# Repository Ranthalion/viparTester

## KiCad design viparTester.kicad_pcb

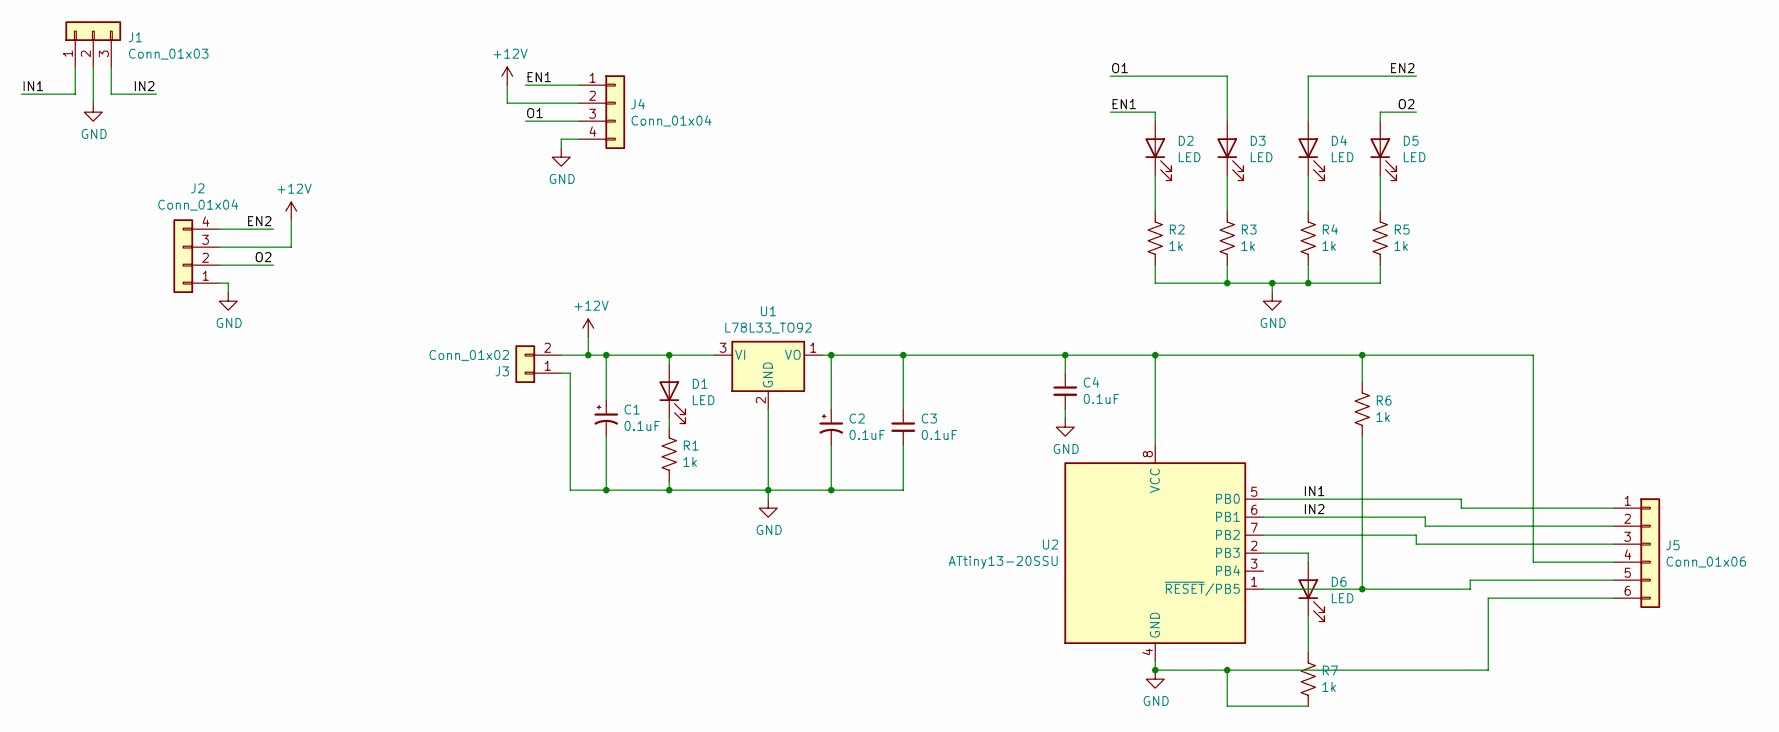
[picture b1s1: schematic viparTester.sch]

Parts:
C1, C2: 0.1uF; CP_Radial_D5.0mm_P2.00mm
C3, C4: 0.1uF; C_1206_3216Metric_Pad1.33x1.80mm_HandSolder
D1, D2, D3, D4, D5, D6: LED; LED_1206_3216Metric_Pad1.42x1.75mm_HandSolder
J1: Conn_01x03; PinSocket_1x03_P2.54mm_Vertical
J2, J4: Conn_01x04; PinSocket_1x04_P2.54mm_Vertical
J3: Conn_01x02; PinSocket_1x02_P2.54mm_Vertical
J5: Conn_01x06; PinSocket_1x06_P2.54mm_Vertical
R1, R2, R3, R4, R5, R6, R7: 1k; R_1206_3216Metric_Pad1.30x1.75mm_HandSolder
U1: L78L33_TO92; TO-92_Inline
U2: ATtiny13-20SSU; SOIC-8_3.9x4.9mm_P1.27mm

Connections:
+12V: C1.1, D1.2 (A), J2.3, J3.2, J4.2, U1.3 (VI)
/EN1: D2.2 (A), J4.1
/EN2: D4.2 (A), J2.4
/IN1: J1.1, J5.1, U2.5 (PB0)
/IN2: J1.3, J5.2, U2.6 (PB1)
/O1: D3.2 (A), J4.3
/O2: D5.2 (A), J2.2
GND: C1.2, C2.2, C3.2, C4.2, J1.2, J2.1, J3.1, J4.4, J5.6, R1.2, R2.2, R3.2, R4.2, R5.2, R7.2, U1.2 (GND), U2.4 (GND)
unnamed: C2.1, C3.1, C4.1, J5.4, R6.1, U1.1 (VO), U2.8 (VCC)
unnamed: D1.1 (K), R1.1
unnamed: D2.1 (K), R2.1
unnamed: D3.1 (K), R3.1
unnamed: D4.1 (K), R4.1
unnamed: D5.1 (K), R5.1
unnamed: D6.1 (K), R7.1
unnamed: D6.2 (A), U2.2 (PB3)
unnamed: J5.3, U2.7 (PB2)
unnamed: J5.5, R6.2, U2.1 (~RESET~/PB5)

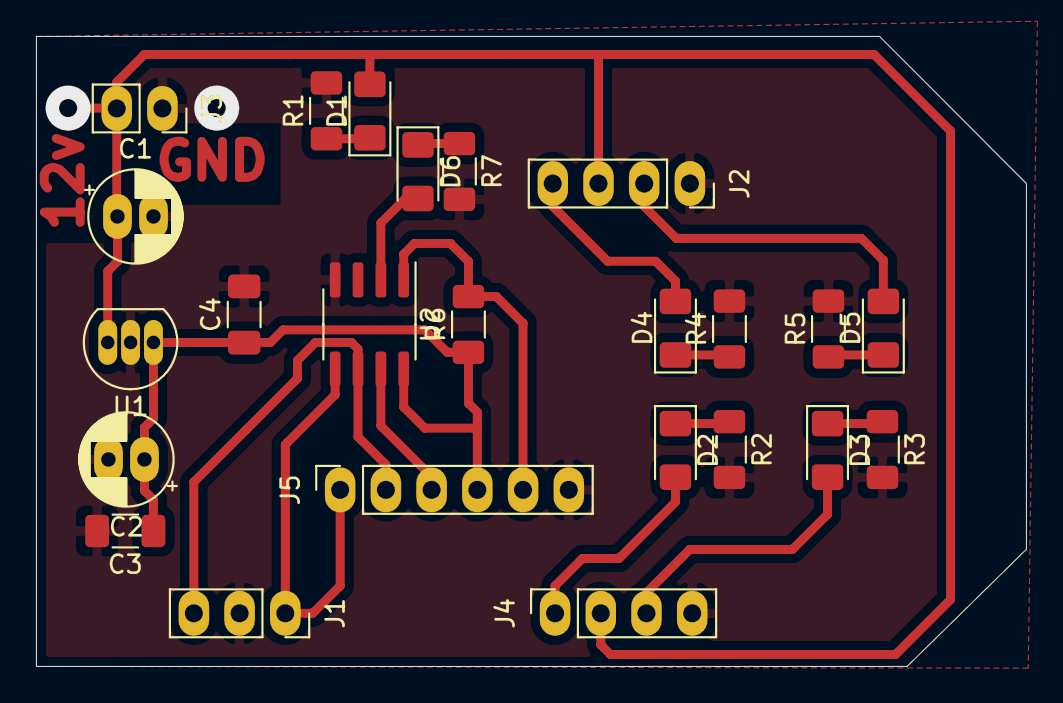
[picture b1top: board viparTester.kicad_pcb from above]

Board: 2 copper layers, 55.0 x 35.0 mm, 24 parts (0 on the bottom side), 18 nets.

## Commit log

2021-03-21 Tester
2021-03-21 gerbers and milling
2021-03-22 firmware
